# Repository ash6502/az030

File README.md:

# az030 - a 68030-based homebrew computer
**! AI DISCLAIMER !**

Claude Code was used in the creation of this

# info

this project is something im working on and have been working on for about a few weeks now (?)

i am currently 15 right now, and have been working on this in my free time, as a labour of love for computers

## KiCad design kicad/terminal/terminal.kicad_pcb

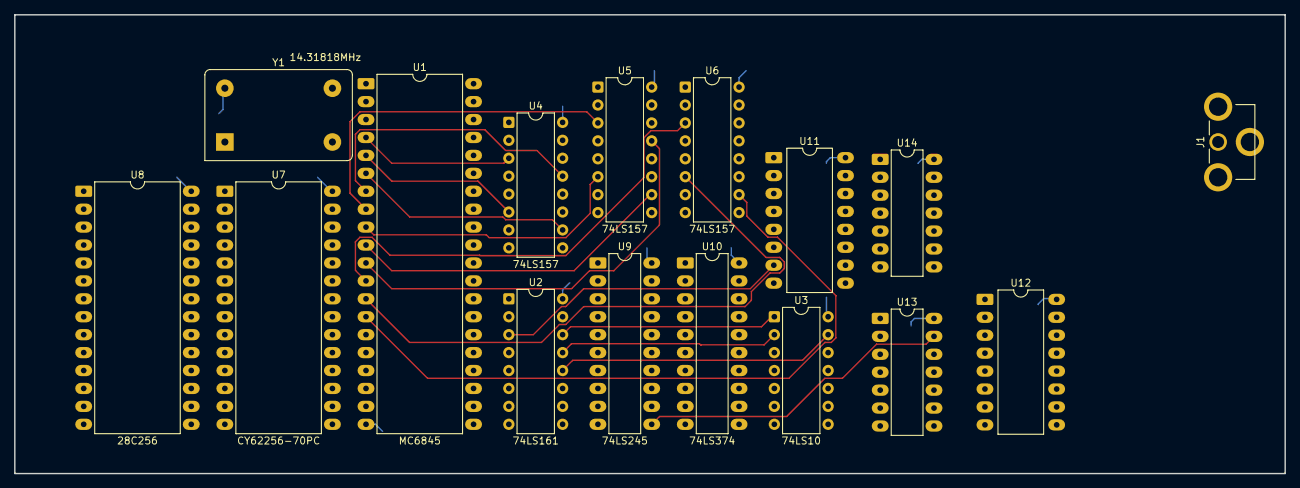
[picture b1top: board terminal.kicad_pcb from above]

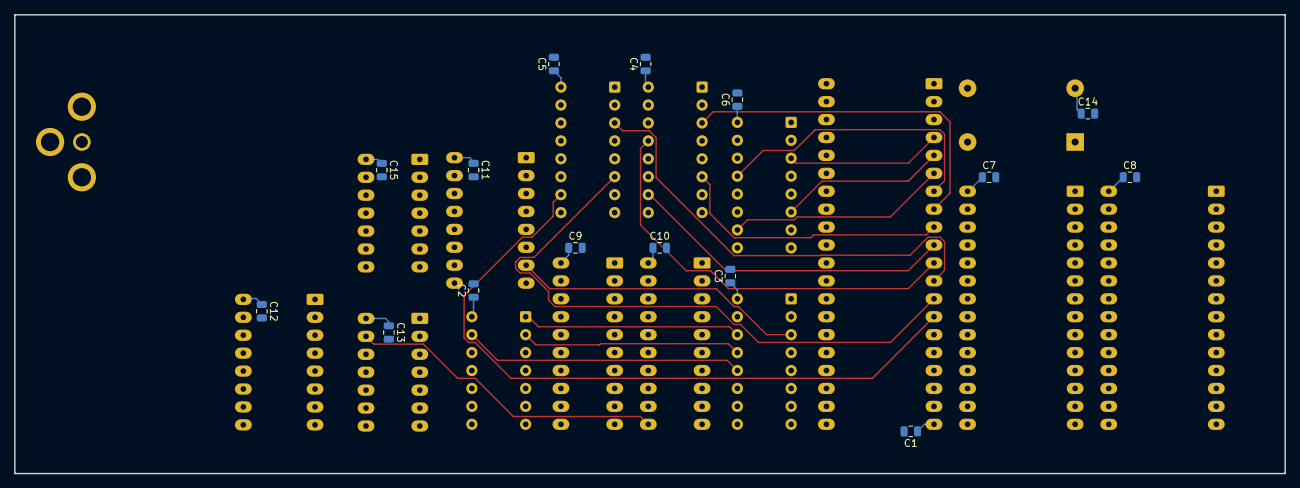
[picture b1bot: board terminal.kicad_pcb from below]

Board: 2 copper layers, 180.0 x 65.0 mm, 31 parts (15 on the bottom side), 43 nets.

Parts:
C1, C2, C3, C4, C5, C6, C7, C8, C9, C10, C11, C12, C13, C14, C15: 100n; C_0805_2012Metric
J1: Conn_Coaxial; RCJ-014
U1: MC6845; DIP-40_W15.24mm_LongPads
U2: 74LS161; DIP-16_W7.62mm
U3: 74LS10; DIP-14_W7.62mm
U4, U5, U6: 74LS157; DIP-16_W7.62mm
U7: CY62256-70PC; DIP-28_W15.24mm_LongPads
U8: 28C256; DIP-28_W15.24mm_LongPads
U9: 74LS245; DIP-20_W7.62mm_LongPads
U10: 74LS374; DIP-20_W7.62mm_LongPads
U11: 74LS166; DIP-16_W10.16mm_LongPads
U12: 74LS174; DIP-16_W10.16mm_LongPads
U13: 74HC86; DIP-14_W7.62mm_LongPads
U14: 74LS04; DIP-14_W7.62mm_LongPads
Y1: 14.31818MHz; Oscillator_DIP-14_LargePads

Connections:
+5V: C1.1, C2.1, C3.1, C4.1, C5.1, C6.1, C7.1, C8.1, C9.1, C10.1, C11.1, C12.1, C13.1, C14.1, C15.1, U1.20 (VCC), U2.16 (VCC), U3.14 (VCC), U4.16 (VCC), U5.16 (VCC), U6.16 (VCC), U7.28 (VCC), U8.28 (VCC), U9.20 (VCC), U10.20 (VCC), U11.16 (VCC), U12.16 (VCC), U13.14 (VCC), U14.14 (VCC), Y1.14 (Vcc)
/D0: U7.11 (Q0), U8.11 (D0)
/D1: U7.12 (Q1), U8.12 (D1)
/D2: U7.13 (Q2), U8.13 (D2)
/D3: U7.15 (Q3), U8.15 (D3)
/D4: U7.16 (Q4), U8.16 (D4)
/D5: U7.17 (Q5), U8.17 (D5)
/D6: U7.18 (Q6), U8.18 (D6)
/D7: U7.19 (Q7), U8.19 (D7)
/MA0: U1.4 (MA0), U4.3 (I1a)
/MA1: U1.5 (MA1), U4.6 (I1b)
/MA2: U1.6 (MA2), U4.10 (I1c)
/MA3: U1.7 (MA3), U4.13 (I1d)
/MA4: U1.8 (MA4), U5.3 (I1a)
/MA5: U1.9 (MA5), U5.6 (I1b)
/MA6: U1.10 (MA6), U5.10 (I1c)
/MA7: U1.11 (MA7), U5.13 (I1d)
/MA8: U1.12 (MA8), U6.3 (I1a)
/MA9: U1.13 (MA9), U6.6 (I1b)
/MA10: U1.14 (MA10), U6.10 (I1c)
/RAMA0: U5.4 (Za), U7.10 (A0)
/RAMA1: U5.7 (Zb), U7.9 (A1)
/RAMA2: U5.9 (Zc), U7.8 (A2)
/RAMA3: U5.12 (Zd), U7.7 (A3)
/RAMA4: U6.4 (Za), U7.6 (A4)
/RAMA5: U6.7 (Zb), U7.5 (A5)
/RAMA6: U6.9 (Zc), U7.4 (A6)
/RAMA7: U6.12 (Zd), U7.3 (A7)
/RAMA8: U4.4 (Za), U7.25 (A8)
/RAMA9: U4.7 (Zb), U7.24 (A9)
/RAMA10: U4.9 (Zc), U7.23 (A11)
CRTC_CLK: U1.21 (CLK), U13.11
DOTCLK: U2.3 (D0), U11.7 (Clk), Y1.8 (OUT)
GND: C1.2, C2.2, C3.2, C4.2, C5.2, C6.2, C7.2, C8.2, C9.2, C10.2, C11.2, C12.2, C13.2, C14.2, C15.2, U1.1 (GND), U2.8 (GND), U3.7 (GND), U4.8 (GND), U5.8 (GND), U6.8 (GND), U7.14 (GND), U8.14 (GND), U9.10 (GND), U10.10 (GND), U11.8 (GND), U12.8 (GND), U13.7 (GND), U14.7 (GND), Y1.7 (GND)
QA: U2.14 (Q0), U3.1
QB: U2.13 (Q1), U3.2, U13.12
QC: U2.12 (Q2), U3.13, U14.1
VRAM: U3.4, U3.9, U14.4
W: U3.5, U3.10, U14.6
~LD: U3.12, U11.15 (PE)
~QC: U9.11 (B7), U12.9 (Cp), U13.13, U14.2
~VWE: U3.6, U7.21 (A10)
~VWRCYC: U3.8, U14.9

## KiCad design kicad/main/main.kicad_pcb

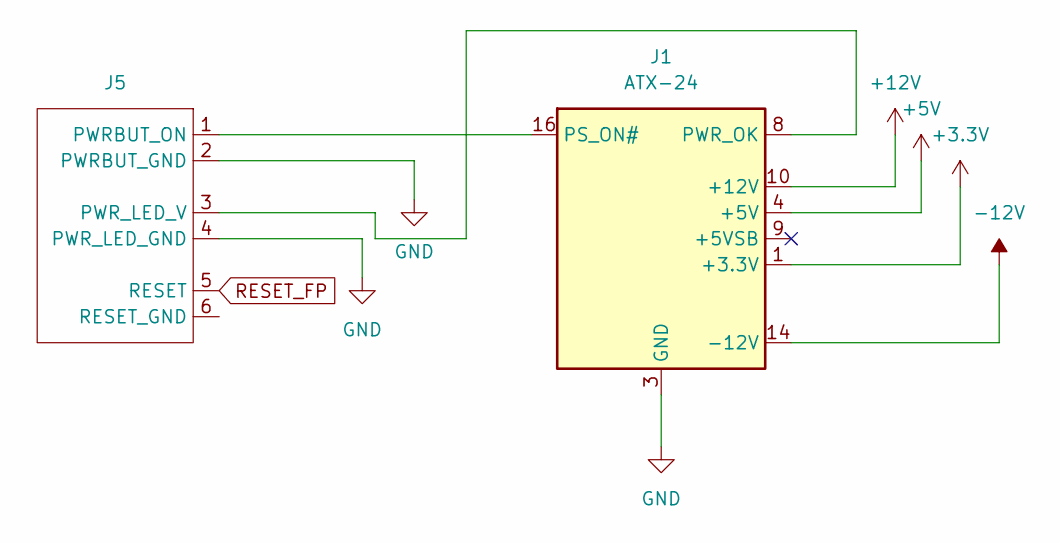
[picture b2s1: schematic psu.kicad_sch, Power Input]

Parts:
J1: ATX-24; Molex_Mini-Fit_Jr_5566-24A_2x12_P4.20mm_Vertical
J5: PinHeader_2x03_P2.54mm_Vertical

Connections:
+3.3V: J1.1 (+3.3V), J1.2 (+3.3V), J1.12 (+3.3V), J1.13 (+3.3V)
+5V: J1.4 (+5V), J1.6 (+5V), J1.21 (+5V), J1.22 (+5V), J1.23 (+5V); also elsewhere on the board
+12V: J1.10 (+12V), J1.11 (+12V)
-12V: J1.14 (-12V)
GND: J1.3 (GND), J1.5 (GND), J1.7 (GND), J1.15 (GND), J1.17 (GND), J1.18 (GND), J1.19 (GND), J1.24 (GND), J5.2 (PWRBUT_GND), J5.4 (PWR_LED_GND); also elsewhere on the board
unnamed: J1.16 (PS_ON#), J5.1 (PWRBUT_ON)
unnamed: J1.8 (PWR_OK), J5.3 (PWR_LED_V)
RESET_FP: J5.5 (RESET); also elsewhere on the board

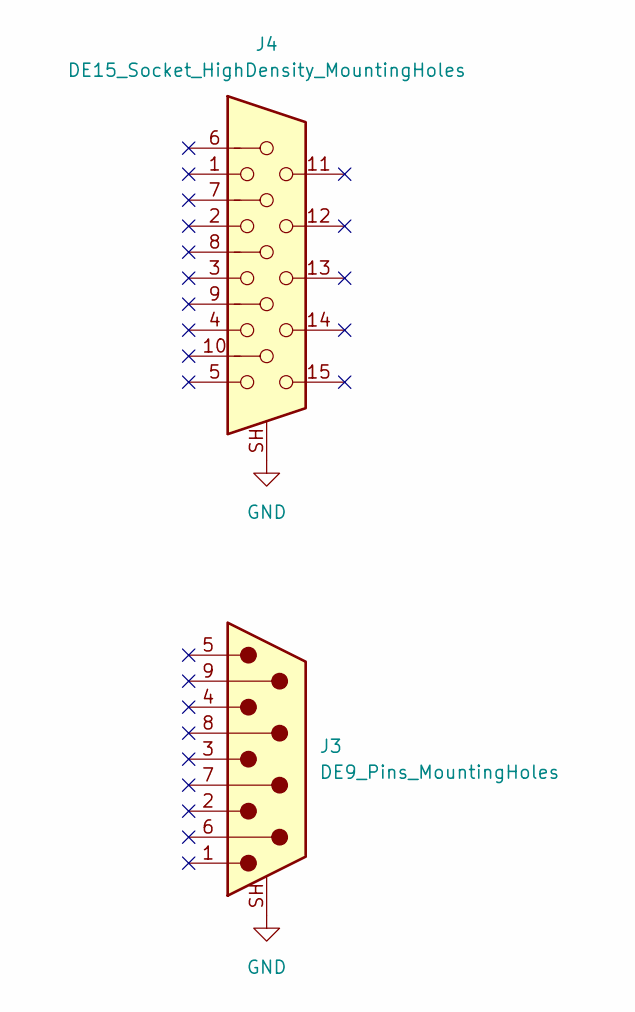
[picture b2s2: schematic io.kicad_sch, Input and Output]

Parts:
J3: DE9_Pins_MountingHoles; DSUB-9_Pins_Horizontal_P2.77x2.84mm_EdgePinOffset4.94mm_Hou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
J4: DE15_Socket_HighDensity_MountingHoles; DSUB-15_Socket_Horizontal_P2.77x2.84mm_EdgePinOffset4.94mm_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

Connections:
GND: J3.SH (PAD_SH), J4.SH; also elsewhere on the board

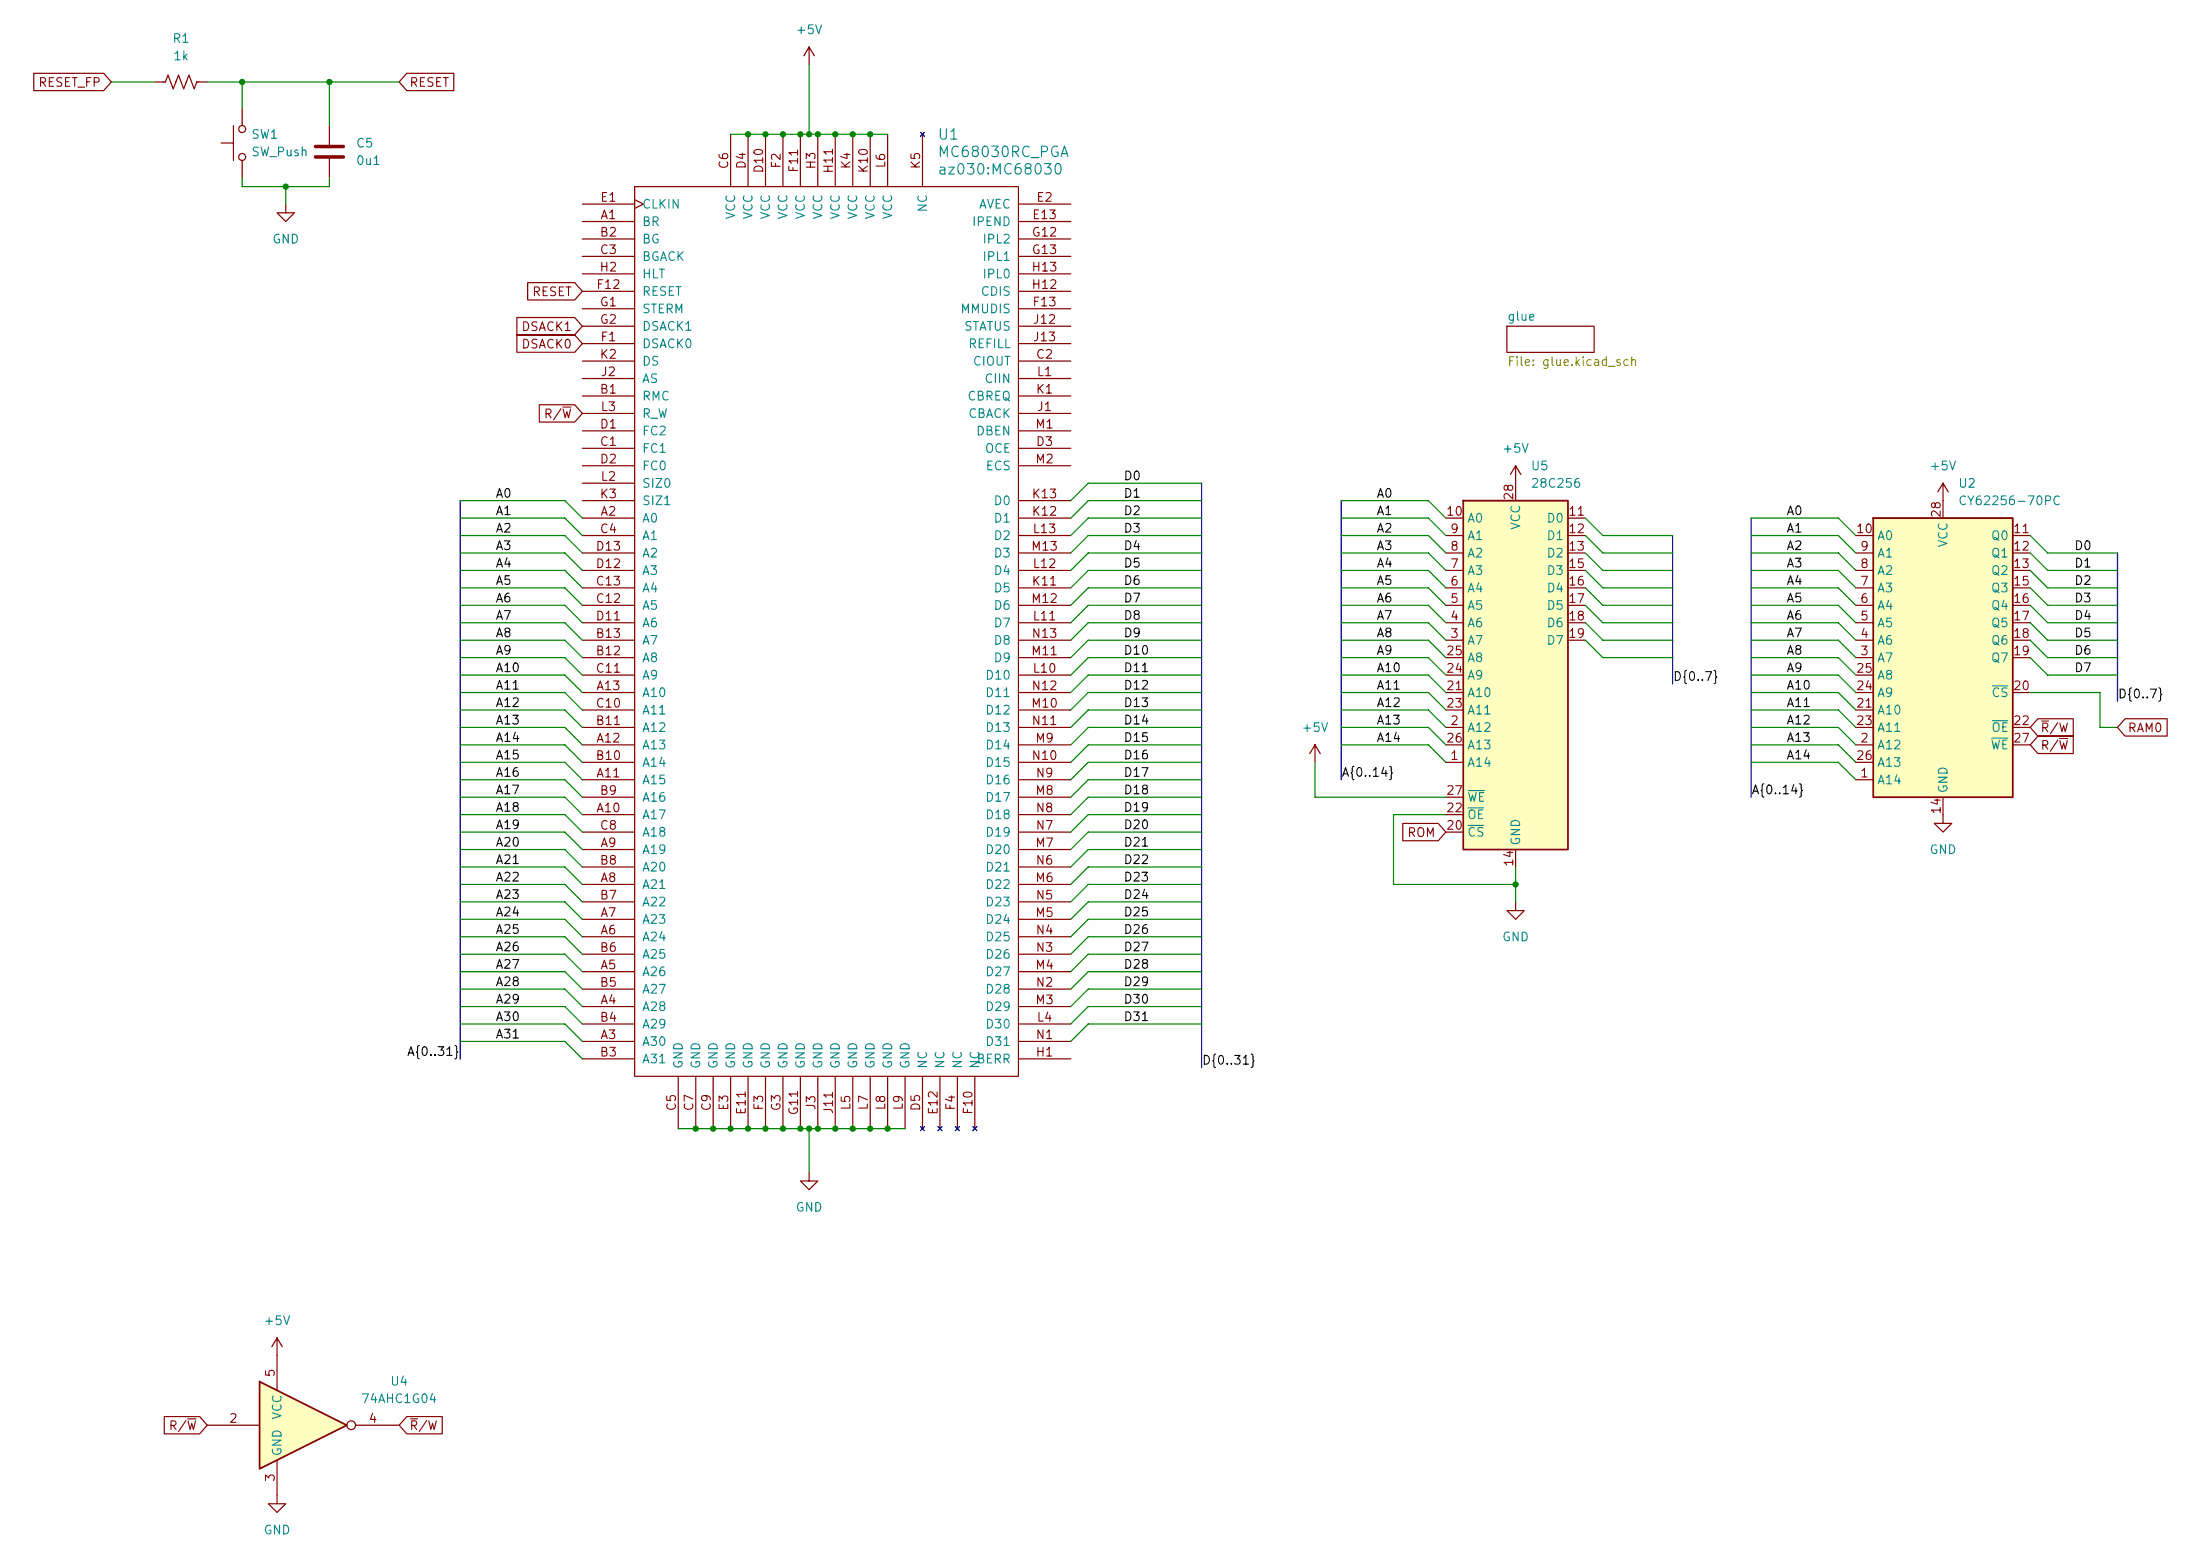
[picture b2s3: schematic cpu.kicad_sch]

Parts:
C5: 0u1
R1: 1k; R_Axial_DIN0204_L3.6mm_D1.6mm_P5.08mm_Horizontal
SW1: SW_Push; SW_PUSH_6mm
U1: MC68030RC_PGA; MC68030
U2: CY62256-70PC; DIP-28_W15.24mm_LongPads
U4: 74AHC1G04; SOT-553
U5: 28C256; DIP-28_W15.24mm_Socket_LongPads

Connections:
+5V: U1.C6 (VCC), U1.D4 (VCC), U1.D10 (VCC), U1.F2 (VCC), U1.F11 (VCC), U1.H3 (VCC), U1.H11 (VCC), U1.K4 (VCC), U1.K10 (VCC), U1.L6 (VCC), U2.28 (VCC), U4.5 (VCC), U5.27 (~WE), U5.28 (VCC); also elsewhere on the board
/cpu/A0: U1.A2 (A0), U2.10 (A0), U5.10 (A0)
/cpu/A1: U1.C4 (A1), U2.9 (A1), U5.9 (A1)
/cpu/A2: U1.D13 (A2), U2.8 (A2), U5.8 (A2)
/cpu/A3: U1.D12 (A3), U2.7 (A3), U5.7 (A3)
/cpu/A4: U1.C13 (A4), U2.6 (A4), U5.6 (A4)
/cpu/A5: U1.C12 (A5), U2.5 (A5), U5.5 (A5)
/cpu/A6: U1.D11 (A6), U2.4 (A6), U5.4 (A6)
/cpu/A7: U1.B13 (A7), U2.3 (A7), U5.3 (A7)
/cpu/A8: U1.B12 (A8), U2.25 (A8), U5.25 (A8)
/cpu/A9: U1.C11 (A9), U2.24 (A9), U5.24 (A9)
/cpu/A10: U1.A13 (A10), U2.21 (A10), U5.21 (A10)
/cpu/A11: U1.C10 (A11), U2.23 (A11), U5.23 (A11)
/cpu/A12: U1.B11 (A12), U2.2 (A12), U5.2 (A12)
/cpu/A13: U1.A12 (A13), U2.26 (A13), U5.26 (A13)
/cpu/A14: U1.B10 (A14), U2.1 (A14), U5.1 (A14)
/cpu/A15: U1.A11 (A15)
/cpu/A16: U1.B9 (A16)
/cpu/A17: U1.A10 (A17)
/cpu/A18: U1.C8 (A18)
/cpu/A19: U1.A9 (A19)
/cpu/A20: U1.B8 (A20)
/cpu/A21: U1.A8 (A21)
/cpu/A22: U1.B7 (A22)
/cpu/A23: U1.A7 (A23)
/cpu/A24: U1.A6 (A24)
/cpu/A25: U1.B6 (A25)
/cpu/A26: U1.A5 (A26)
/cpu/A27: U1.B5 (A27)
/cpu/A28: U1.A4 (A28)
/cpu/A29: U1.B4 (A29)
/cpu/A30: U1.A3 (A30)
/cpu/A31: U1.B3 (A31)
/cpu/D0: U1.K13 (D0), U2.11 (Q0)
/cpu/D1: U1.K12 (D1), U2.12 (Q1)
/cpu/D2: U1.L13 (D2), U2.13 (Q2)
/cpu/D3: U1.M13 (D3), U2.15 (Q3)
/cpu/D4: U1.L12 (D4), U2.16 (Q4)
/cpu/D5: U1.K11 (D5), U2.17 (Q5)
/cpu/D6: U1.M12 (D6), U2.18 (Q6)
/cpu/D7: U1.L11 (D7), U2.19 (Q7)
/cpu/D8: U1.N13 (D8)
/cpu/D9: U1.M11 (D9)
/cpu/D10: U1.L10 (D10)
/cpu/D11: U1.N12 (D11)
/cpu/D12: U1.M10 (D12)
/cpu/D13: U1.N11 (D13)
/cpu/D14: U1.M9 (D14)
/cpu/D15: U1.N10 (D15)
/cpu/D16: U1.N9 (D16)
/cpu/D17: U1.M8 (D17)
/cpu/D18: U1.N8 (D18)
/cpu/D19: U1.N7 (D19)
/cpu/D20: U1.M7 (D20)
/cpu/D21: U1.N6 (D21)
/cpu/D22: U1.M6 (D22)
/cpu/D23: U1.N5 (D23)
/cpu/D24: U1.M5 (D24)
/cpu/D25: U1.N4 (D25)
/cpu/D26: U1.N3 (D26)
/cpu/D27: U1.M4 (D27)
/cpu/D28: U1.N2 (D28)
/cpu/D29: U1.M3 (D29)
/cpu/D30: U1.L4 (D30)
/cpu/D31: U1.N1 (D31)
DSACK0: U1.F1 (DSACK0)
DSACK1: U1.G2 (DSACK1); also elsewhere on the board
GND: C5.2, SW1.1, U1.C5 (GND), U1.C7 (GND), U1.C9 (GND), U1.E3 (GND), U1.E11 (GND), U1.F3 (GND), U1.G3 (GND), U1.G11 (GND), U1.J3 (GND), U1.J11 (GND), U1.L5 (GND), U1.L7 (GND), U1.L8 (GND), U1.L9 (GND), U2.14 (GND), U4.3 (GND), U5.14 (GND), U5.22 (~OE); also elsewhere on the board
RAM0: U2.20 (~CS); also elsewhere on the board
RESET: C5.1, R1.2, SW1.2, U1.F12 (RESET)
RESET_FP: R1.1; also elsewhere on the board
ROM: U5.20 (~CS); also elsewhere on the board
R/~W: U1.L3 (R_W), U2.27 (~WE), U4.2
~R/W: U2.22 (~OE), U4.4

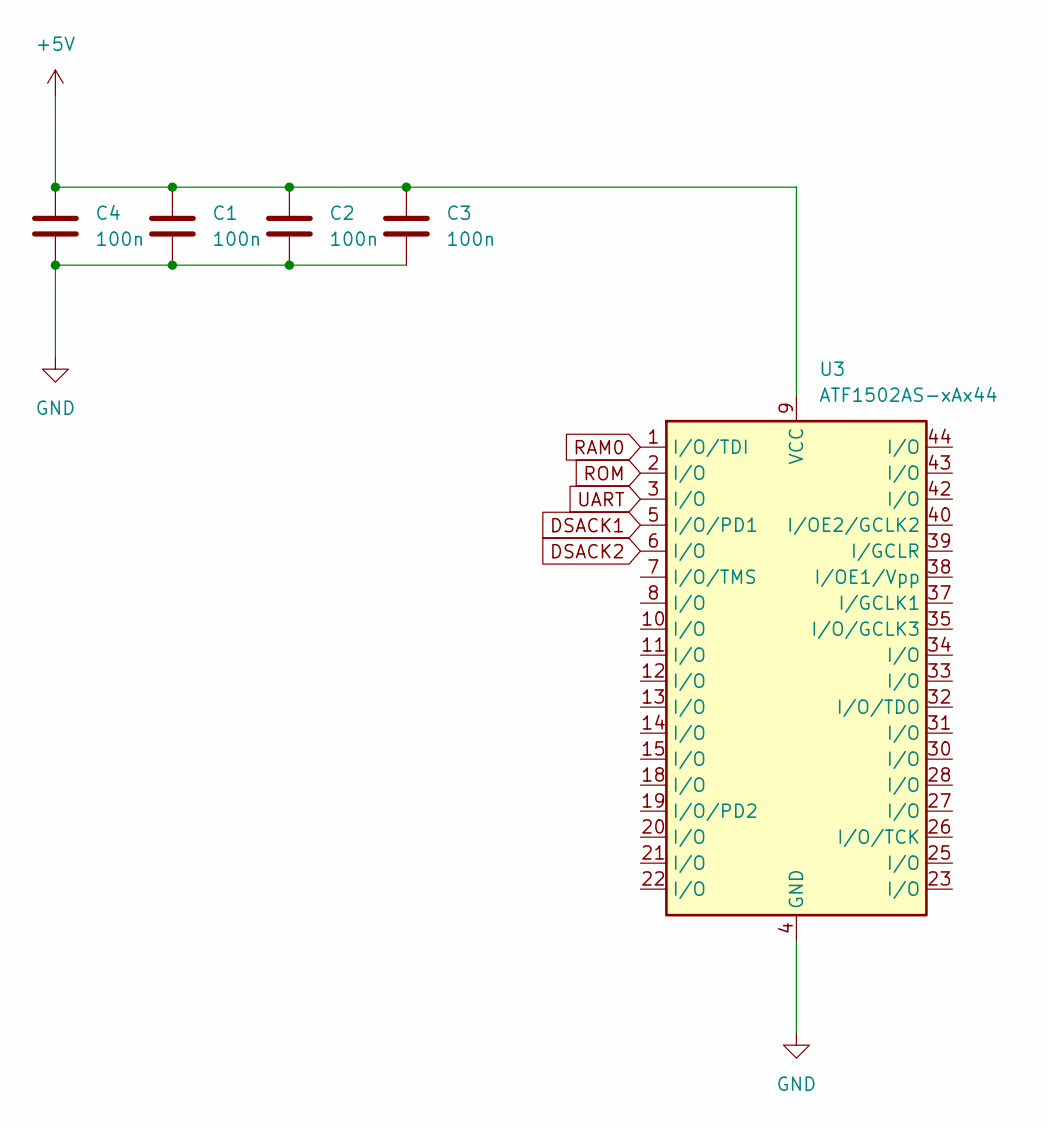
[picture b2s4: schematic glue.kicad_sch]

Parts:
C1, C2, C3, C4: 100n; C_0603_1608Metric
U3: ATF1502AS-xAx44; TQFP-44_10x10mm_P0.8mm

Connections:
+5V: C1.1, C2.1, C3.1, C4.1, U3.9 (VCC), U3.17 (VCC), U3.29 (VCC), U3.41 (VCC); also elsewhere on the board
DSACK1: U3.5 (I/O/PD1); also elsewhere on the board
DSACK2: U3.6 (I/O)
GND: C1.2, C2.2, C3.2, C4.2, U3.4 (GND), U3.16 (GND), U3.24 (GND), U3.36 (GND); also elsewhere on the board
RAM0: U3.1 (I/O/TDI); also elsewhere on the board
ROM: U3.2 (I/O); also elsewhere on the board
UART: U3.3 (I/O)

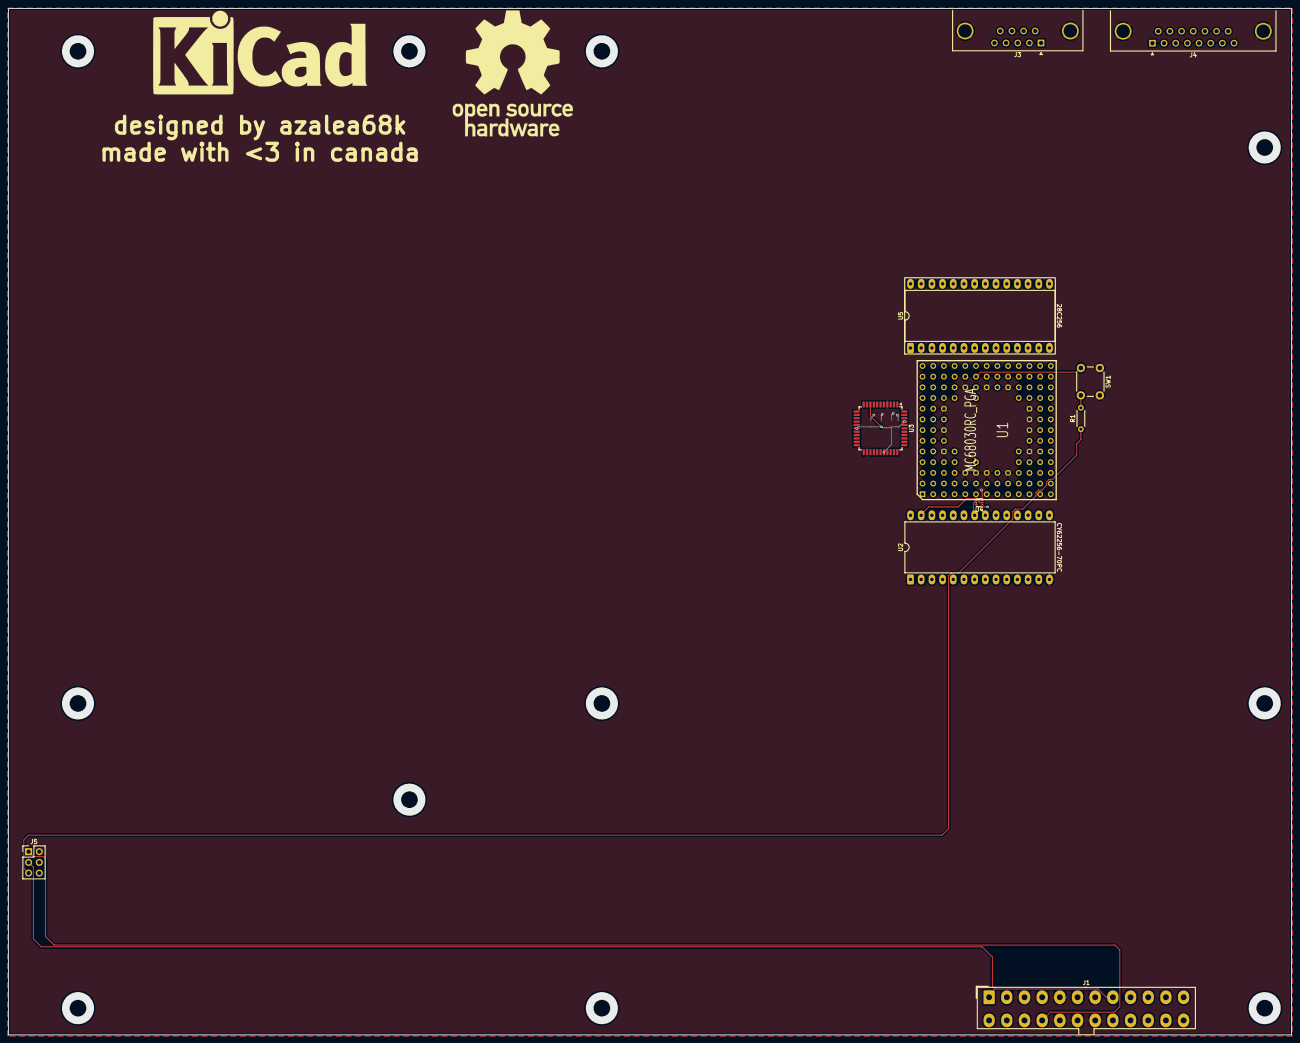
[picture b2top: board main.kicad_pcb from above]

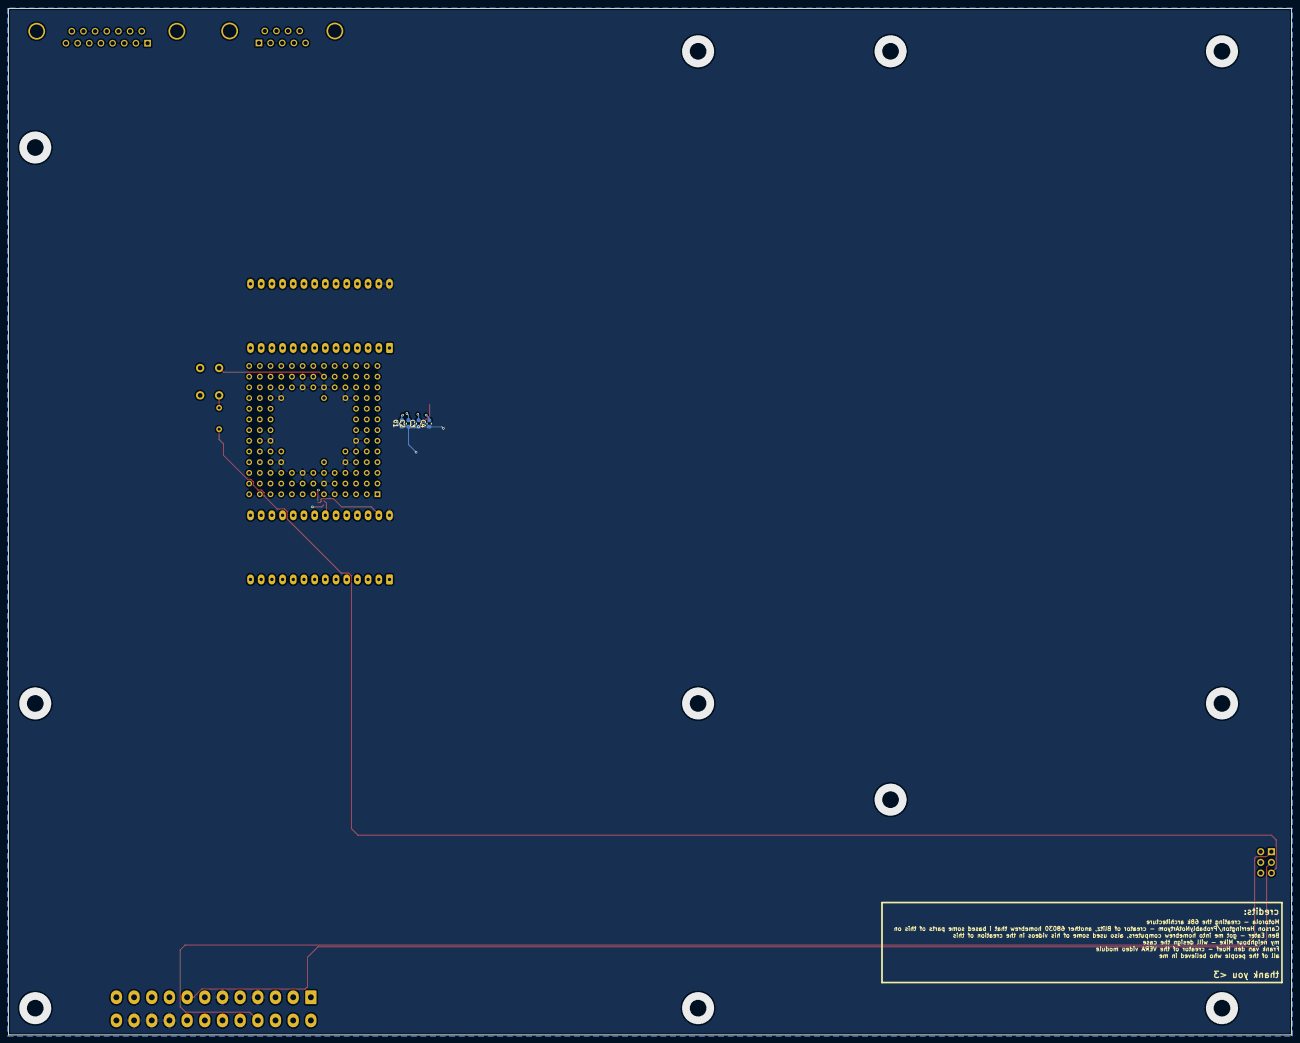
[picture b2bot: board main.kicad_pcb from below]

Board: 2 copper layers, 304.8 x 243.8 mm, 15 parts (4 on the bottom side), 36 nets.

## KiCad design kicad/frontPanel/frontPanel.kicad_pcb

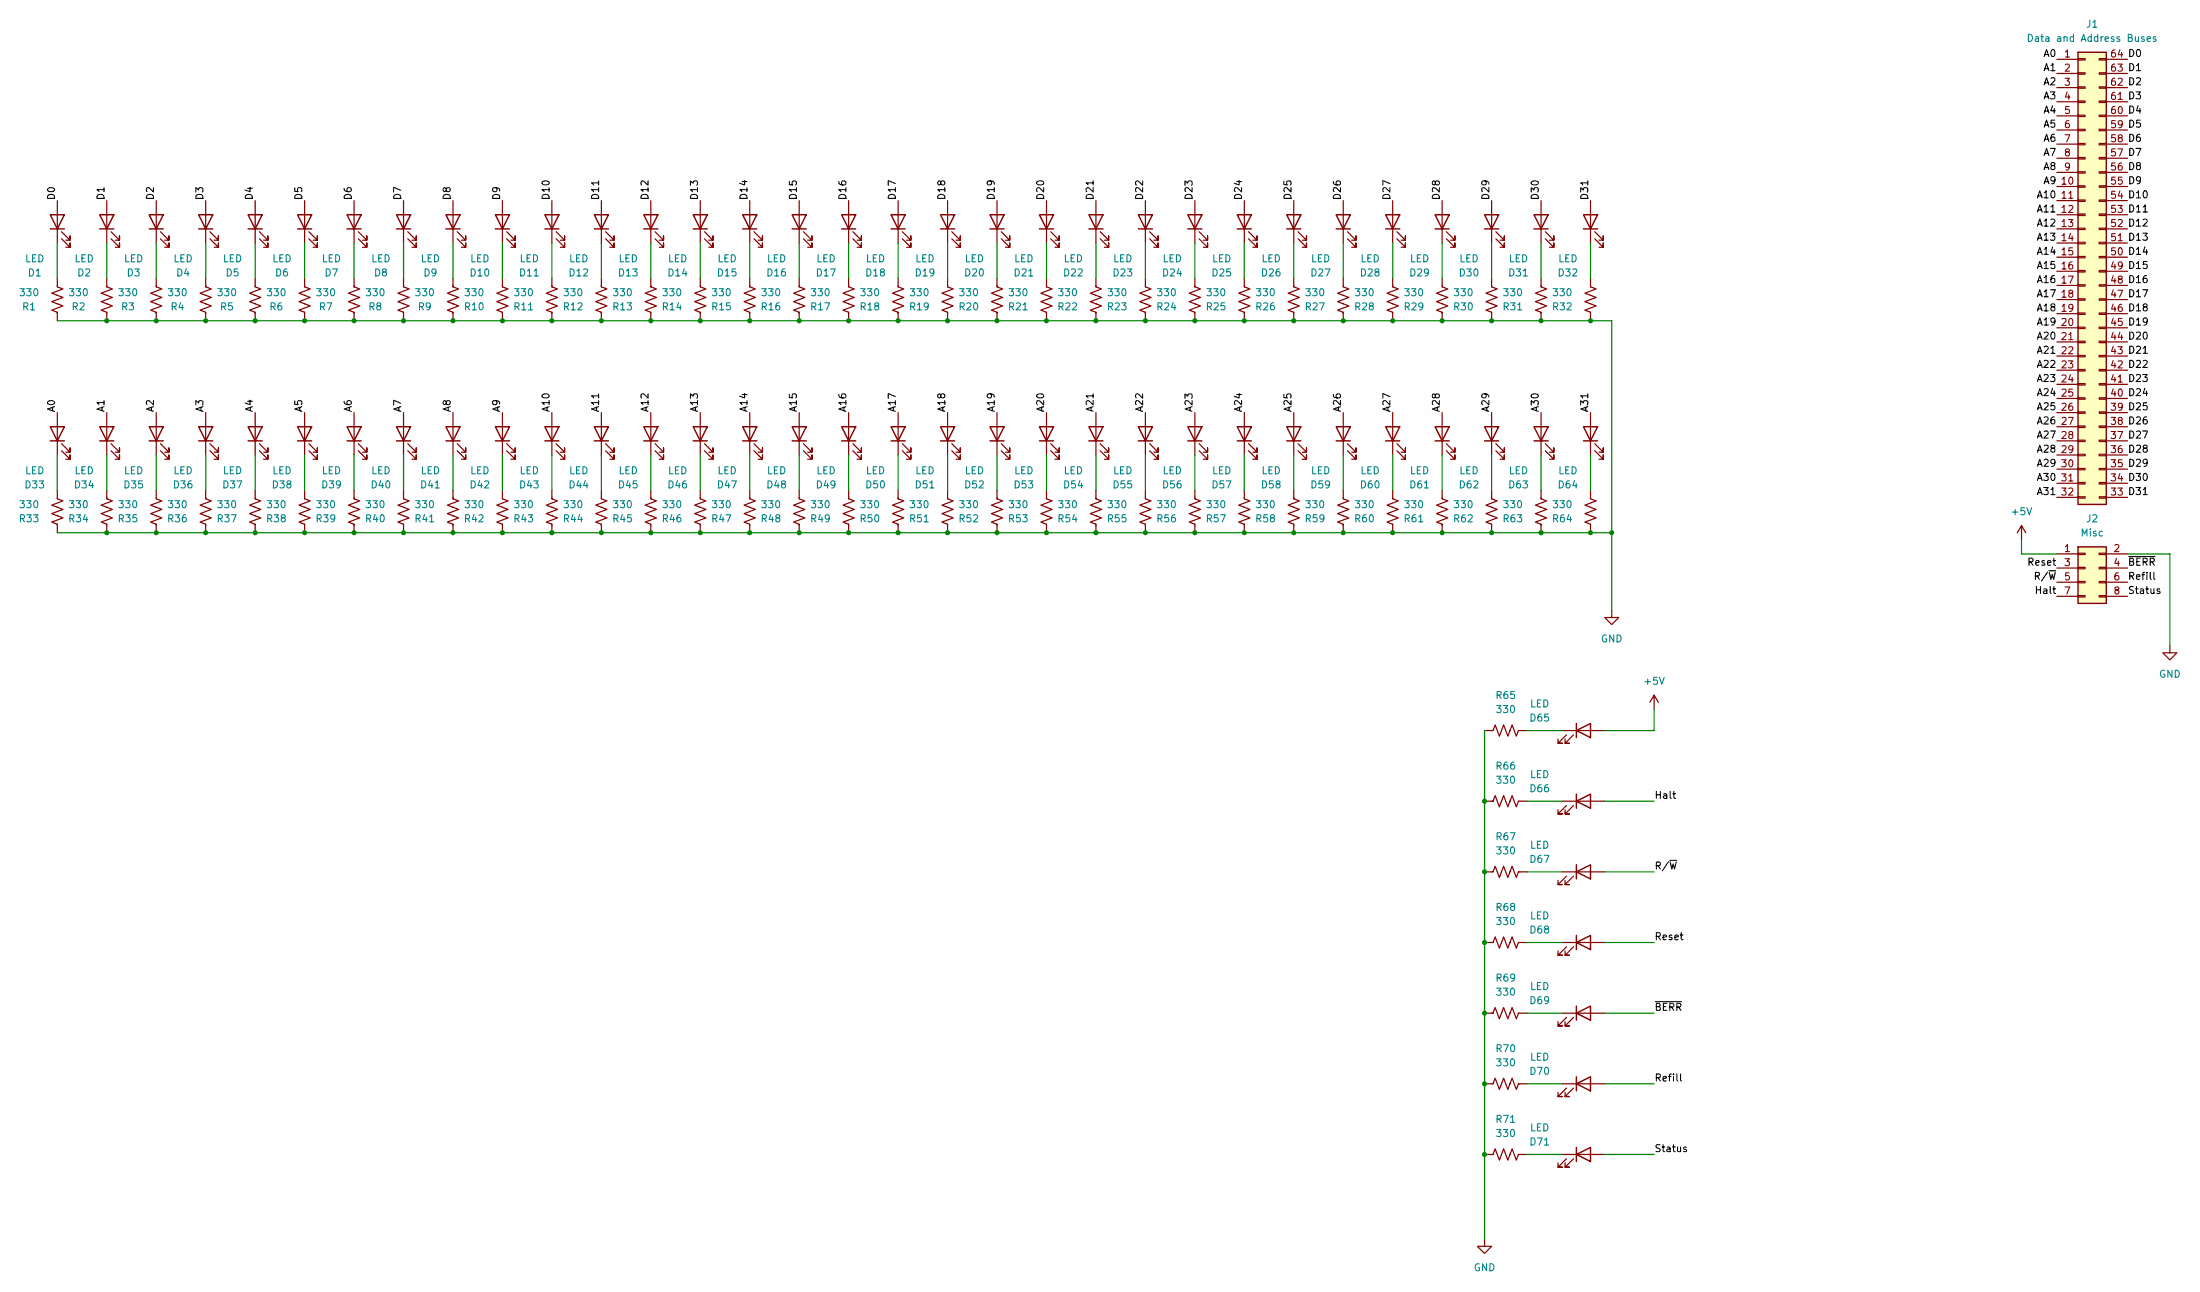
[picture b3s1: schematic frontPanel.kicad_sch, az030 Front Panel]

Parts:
D1, D2, D3, D4, D5, D6, D7, D8, D9, D10, D11, D12, D13, D14, D15, D16, D17, D18, D19, D20, D21, D22, D23, D24, D25, D26, D27, D28, D29, D30, D31, D32, D33, D34, D35, D36, D37, D38, D39, D40, D41, D42, D43, D44, D45, D46, D47, D48, D49, D50, D51, D52, D53, D54, D55, D56, D57, D58, D59, D60, D61, D62, D63, D64, D65, D66, D67, D68, D69, D70, D71: LED; LED_D5.0mm
J1: Data and Address Buses; IDC-Header_2x32_P2.54mm_Vertical
J2: Misc; IDC-Header_2x04_P2.54mm_Vertical
R1, R2, R3, R4, R5, R6, R7, R8, R9, R10, R11, R12, R13, R14, R15, R16, R17, R18, R19, R20, R21, R22, R23, R24, R25, R26, R27, R28, R29, R30, R31, R32, R33, R34, R35, R36, R37, R38, R39, R40, R41, R42, R43, R44, R45, R46, R47, R48, R49, R50, R51, R52, R53, R54, R55, R56, R57, R58, R59, R60, R61, R62, R63, R64, R65, R66, R67, R68, R69, R70, R71: 330; R_0603_1608Metric

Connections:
+5V: D65.2 (A), J2.1
/A0: D33.2 (A), J1.1
/A1: D34.2 (A), J1.2
/A2: D35.2 (A), J1.3
/A3: D36.2 (A), J1.4
/A4: D37.2 (A), J1.5
/A5: D38.2 (A), J1.6
/A6: D39.2 (A), J1.7
/A7: D40.2 (A), J1.8
/A8: D41.2 (A), J1.9
/A9: D42.2 (A), J1.10
/A10: D43.2 (A), J1.11
/A11: D44.2 (A), J1.12
/A12: D45.2 (A), J1.13
/A13: D46.2 (A), J1.14
/A14: D47.2 (A), J1.15
/A15: D48.2 (A), J1.16
/A16: D49.2 (A), J1.17
/A17: D50.2 (A), J1.18
/A18: D51.2 (A), J1.19
/A19: D52.2 (A), J1.20
/A20: D53.2 (A), J1.21
/A21: D54.2 (A), J1.22
/A22: D55.2 (A), J1.23
/A23: D56.2 (A), J1.24
/A24: D57.2 (A), J1.25
/A25: D58.2 (A), J1.26
/A26: D59.2 (A), J1.27
/A27: D60.2 (A), J1.28
/A28: D61.2 (A), J1.29
/A29: D62.2 (A), J1.30
/A30: D63.2 (A), J1.31
/A31: D64.2 (A), J1.32
/D0: D1.2 (A), J1.64
/D1: D2.2 (A), J1.63
/D2: D3.2 (A), J1.62
/D3: D4.2 (A), J1.61
/D4: D5.2 (A), J1.60
/D5: D6.2 (A), J1.59
/D6: D7.2 (A), J1.58
/D7: D8.2 (A), J1.57
/D8: D9.2 (A), J1.56
/D9: D10.2 (A), J1.55
/D10: D11.2 (A), J1.54
/D11: D12.2 (A), J1.53
/D12: D13.2 (A), J1.52
/D13: D14.2 (A), J1.51
/D14: D15.2 (A), J1.50
/D15: D16.2 (A), J1.49
/D16: D17.2 (A), J1.48
/D17: D18.2 (A), J1.47
/D18: D19.2 (A), J1.46
/D19: D20.2 (A), J1.45
/D20: D21.2 (A), J1.44
/D21: D22.2 (A), J1.43
/D22: D23.2 (A), J1.42
/D23: D24.2 (A), J1.41
/D24: D25.2 (A), J1.40
/D25: D26.2 (A), J1.39
/D26: D27.2 (A), J1.38
/D27: D28.2 (A), J1.37
/D28: D29.2 (A), J1.36
/D29: D30.2 (A), J1.35
/D30: D31.2 (A), J1.34
/D31: D32.2 (A), J1.33
/Halt: D66.2 (A), J2.7
/Refill: D70.2 (A), J2.6
/Reset: D68.2 (A), J2.3
/R/~W: D67.2 (A), J2.5
/Status: D71.2 (A), J2.8
/~BERR: D69.2 (A), J2.4
GND: J2.2, R1.1, R2.1, R3.1, R4.1, R5.1, R6.1, R7.1, R8.1, R9.1, R10.1, R11.1, R12.1, R13.1, R14.1, R15.1, R16.1, R17.1, R18.1, R19.1, R20.1, R21.1, R22.1, R23.1, R24.1, R25.1, R26.1, R27.1, R28.1, R29.1, R30.1, R31.1, R32.1, R33.1, R34.1, R35.1, R36.1, R37.1, R38.1, R39.1, R40.1, R41.1, R42.1, R43.1, R44.1, R45.1, R46.1, R47.1, R48.1, R49.1, R50.1, R51.1, R52.1, R53.1, R54.1, R55.1, R56.1, R57.1, R58.1, R59.1, R60.1, R61.1, R62.1, R63.1, R64.1, R65.1, R66.1, R67.1, R68.1, R69.1, R70.1, R71.1
unnamed: D1.1 (K), R1.2
unnamed: D2.1 (K), R2.2
unnamed: D3.1 (K), R3.2
unnamed: D4.1 (K), R4.2
unnamed: D5.1 (K), R5.2
unnamed: D6.1 (K), R6.2
unnamed: D7.1 (K), R7.2
unnamed: D8.1 (K), R8.2
unnamed: D9.1 (K), R9.2
unnamed: D10.1 (K), R10.2
unnamed: D11.1 (K), R11.2
unnamed: D12.1 (K), R12.2
unnamed: D13.1 (K), R13.2
unnamed: D14.1 (K), R14.2
unnamed: D15.1 (K), R15.2
unnamed: D16.1 (K), R16.2
unnamed: D17.1 (K), R17.2
unnamed: D18.1 (K), R18.2
unnamed: D19.1 (K), R19.2
unnamed: D20.1 (K), R20.2
unnamed: D21.1 (K), R21.2
unnamed: D22.1 (K), R22.2
unnamed: D23.1 (K), R23.2
unnamed: D24.1 (K), R24.2
unnamed: D25.1 (K), R25.2
unnamed: D26.1 (K), R26.2
unnamed: D27.1 (K), R27.2
unnamed: D28.1 (K), R28.2
unnamed: D29.1 (K), R29.2
unnamed: D30.1 (K), R30.2
unnamed: D31.1 (K), R31.2
unnamed: D32.1 (K), R32.2
unnamed: D33.1 (K), R33.2
unnamed: D34.1 (K), R34.2
unnamed: D35.1 (K), R35.2
unnamed: D36.1 (K), R36.2
unnamed: D37.1 (K), R37.2
unnamed: D38.1 (K), R38.2
unnamed: D39.1 (K), R39.2
unnamed: D40.1 (K), R40.2
unnamed: D41.1 (K), R41.2
unnamed: D42.1 (K), R42.2
unnamed: D43.1 (K), R43.2
unnamed: D44.1 (K), R44.2
unnamed: D45.1 (K), R45.2
unnamed: D46.1 (K), R46.2
unnamed: D47.1 (K), R47.2
unnamed: D48.1 (K), R48.2
unnamed: D49.1 (K), R49.2
unnamed: D50.1 (K), R50.2
unnamed: D51.1 (K), R51.2
unnamed: D52.1 (K), R52.2
unnamed: D53.1 (K), R53.2
unnamed: D54.1 (K), R54.2
unnamed: D55.1 (K), R55.2
unnamed: D56.1 (K), R56.2
unnamed: D57.1 (K), R57.2
unnamed: D58.1 (K), R58.2
unnamed: D59.1 (K), R59.2
unnamed: D60.1 (K), R60.2
unnamed: D61.1 (K), R61.2
unnamed: D62.1 (K), R62.2
unnamed: D63.1 (K), R63.2
unnamed: D64.1 (K), R64.2
unnamed: D65.1 (K), R65.2
unnamed: D66.1 (K), R66.2
unnamed: D67.1 (K), R67.2
unnamed: D68.1 (K), R68.2
unnamed: D69.1 (K), R69.2
unnamed: D70.1 (K), R70.2
unnamed: D71.1 (K), R71.2

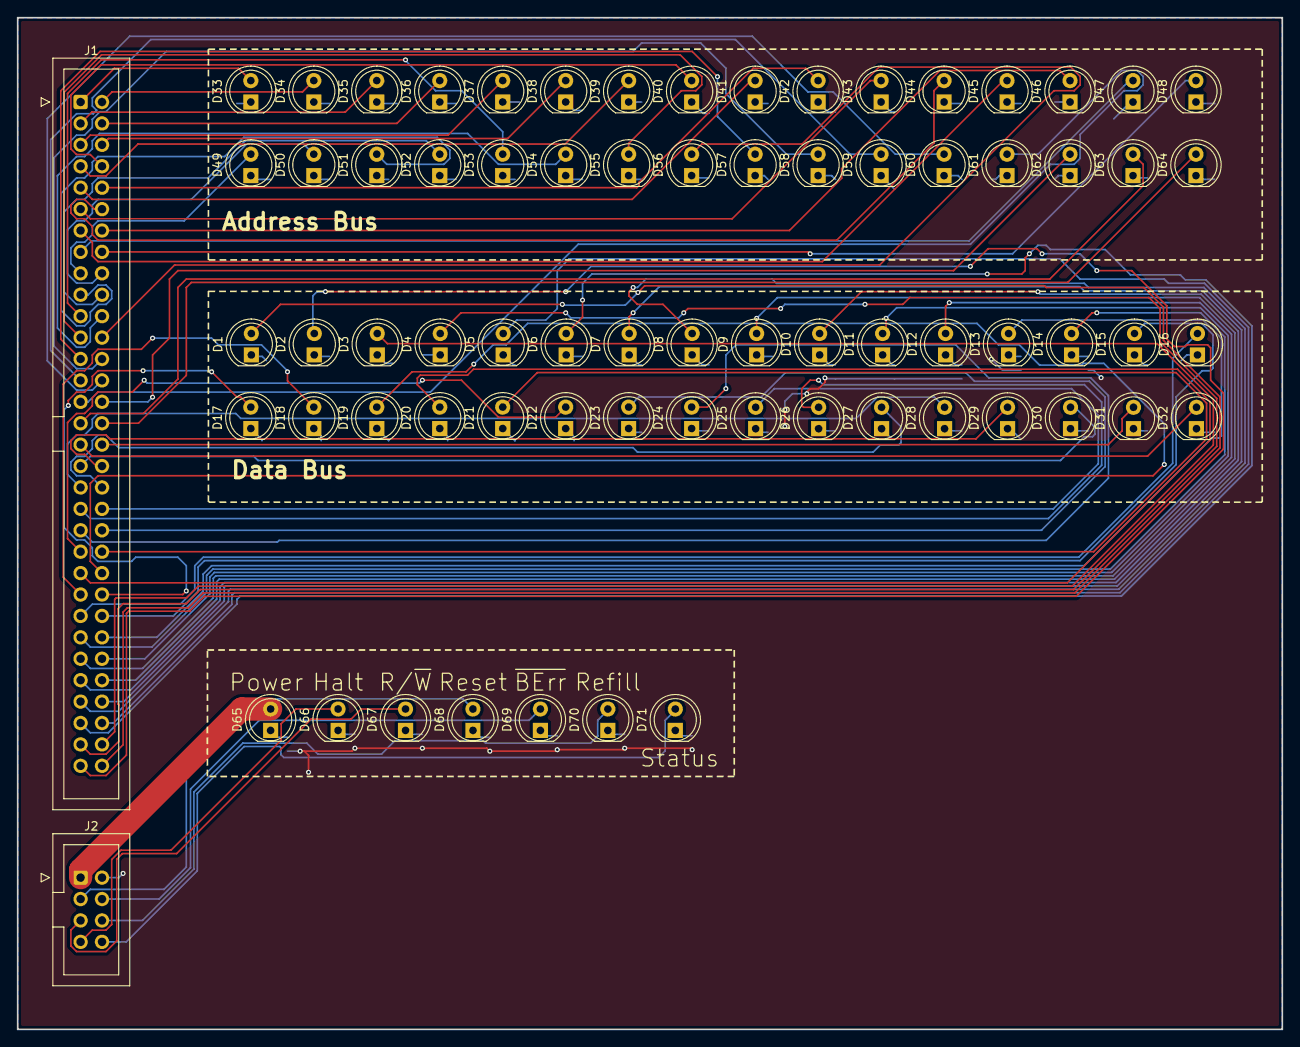
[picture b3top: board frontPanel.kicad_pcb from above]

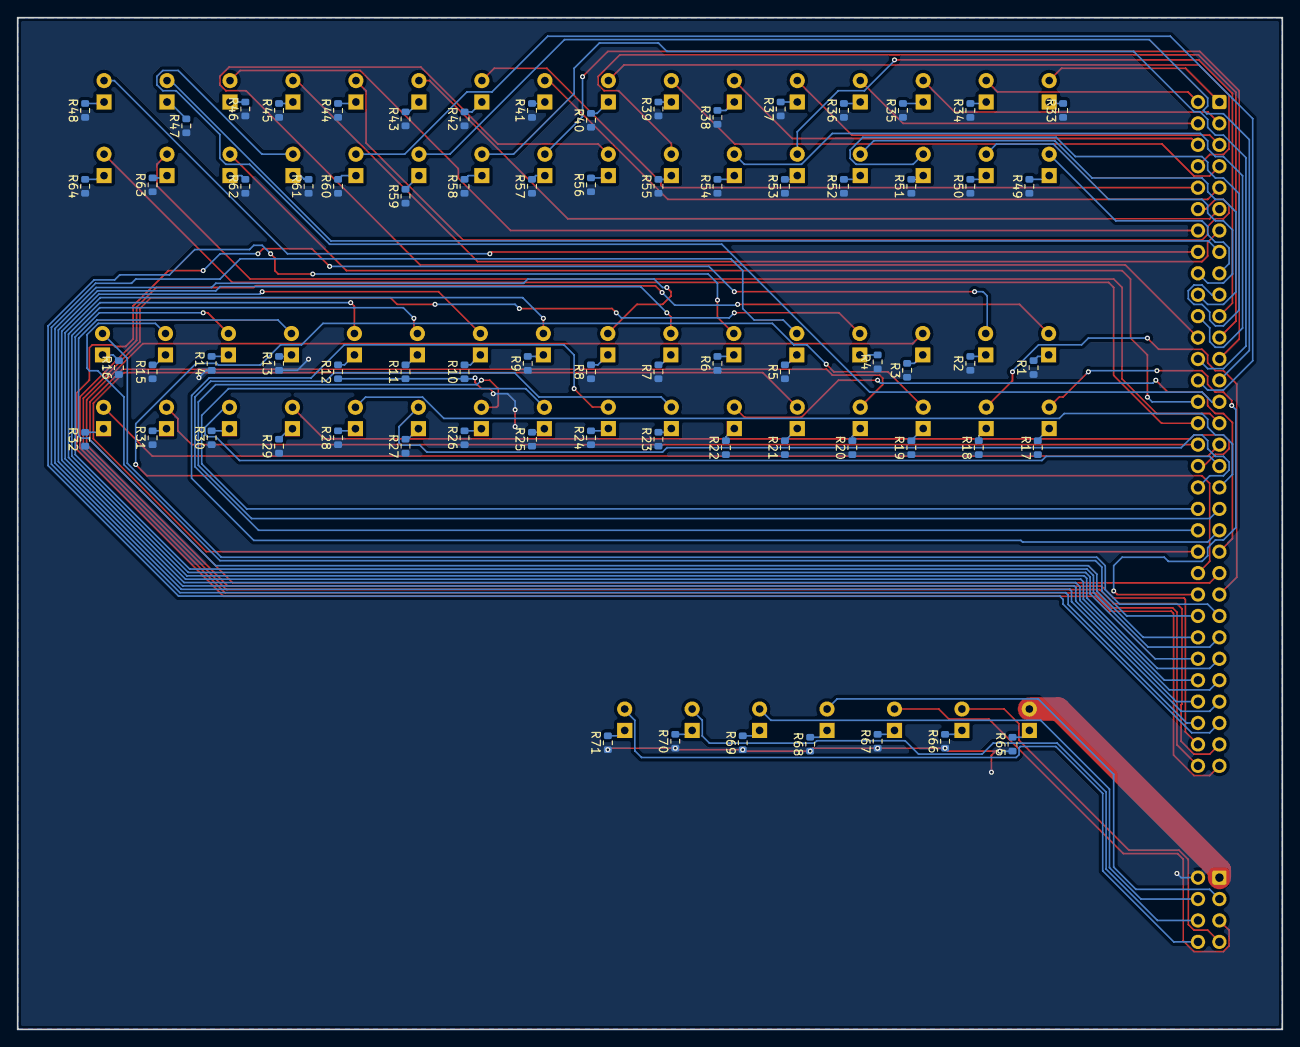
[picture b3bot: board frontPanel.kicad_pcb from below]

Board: 2 copper layers, 150.0 x 120.0 mm, 144 parts (71 on the bottom side), 143 nets.
